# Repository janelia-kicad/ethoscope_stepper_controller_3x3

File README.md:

- [Repository Information](#org758a3eb)
  - [Description](#orgeb4be27)
- [Images](#org71172c4)
- [Schematic](#org945219d)
- [Gerbers](#org1d6248d)
- [Bill of Materials](#orgcc7b03c)
  - [PCB Parts](#orga3dccca)
  - [Supplemental Parts](#org7db11a9)
  - [Vendor Parts Lists](#orgad09c1d)
- [Supplemental Documentation](#org79a2346)
  - [Assembly Instructions](#org838f5a4)

# Repository Information

-   **Name:** ethoscope\_stepper\_controller\_3x3
-   **Version:** 1.2
-   **License:** Open-Source Hardware
-   **URL:** <https://github.com/janelia-kicad/ethoscope_stepper_controller_3x3>
-   **Author:** Peter Polidoro
-   **Email:** peter@polidoro.io

## Description

This device controls the 7 stepper motors on the fly ethoscope rig.

# Images

# Schematic

[./schematic/ethoscope\_stepper\_controller\_3x3.pdf](./schematic/ethoscope_stepper_controller_3x3.pdf)

# Gerbers

Send gerbers zip file to your favorite PCB manufacturer for fabrication.

[./gerbers/ethoscope\_stepper\_controller\_3x3\_v1.2.zip](./gerbers/ethoscope_stepper_controller_3x3_v1.2.zip)

# Bill of Materials

## PCB Parts

| Item | Reference(s)                                     | Quantity | PartNumber       | Vendor  | Description                      |
|---- |------------------------------------------------ |-------- |---------------- |------- |-------------------------------- |
| 1    | C1 C12 C13 C16 C19 C2 C22 C23 C3 C6 C9           | 11       | 1276-1739-1-ND   | digikey | CAP CER 0.1UF 25V Y5V 0402       |
| 2    | C10 C14 C17 C20 C24 C4 C7                        | 7        | 445-14419-1-ND   | digikey | CAP CER 10UF 35V X5R 0805        |
| 3    | C11 C15 C18 C21 C25 C5 C8                        | 7        | 445-9028-1-ND    | digikey | CAP CER 2.2UF 35V X5R 0402       |
| 4    | CLK1                                             | 1        | CTX277LVCT-ND    | digikey | OSC XO 32.000MHZ HCMOS TTL SMD   |
| 5    | L1                                               | 1        | 350-1723-ND      | digikey | LED 2MM 24V VERTICAL RED PC MNT  |
| 6    | L2                                               | 1        | 350-1726-ND      | digikey | LED 2MM 5V VERTICAL GREEN PC MNT |
| 7    | MH1 MH2 MH3 MH4                                  | 4        | 36-2441-ND       | digikey | SHLDR SCREW RND HEAD HEX 4-40    |
| 8    | P1                                               | 1        | CP-015AHPJ-CT-ND | digikey | CONN PWR JACK 2X5.5MM SOLDER     |
| 9    | R1 R15 R8                                        | 3        | P10KJCT-ND       | digikey | RES SMD 10K OHM 5% 1/10W 0402    |
| 10   | R10 R11 R12 R13 R14 R16 R17 R2 R3 R4 R5 R6 R7 R9 | 14       | RL05S2.2FCT-ND   | digikey | RES SMD 2.2 OHM 1% 1/6W 0402     |
| 11   | T1 T2 T3 T4 T5 T6 T7                             | 7        | 277-5738-ND      | digikey | TERM BLOCK HDR 4POS VERT 3.5MM   |
| 12   | TEENSY1                                          | 1        | 1568-1464-ND     | digikey | TEENSY 3.5 (HEADERS)             |
| 13   | U1 U11 U6                                        | 3        | 1460-1071-1-ND   | digikey | IC MOTOR CONTROLLER SPI 32QFN    |
| 14   | U10 U13 U3 U4 U5 U8 U9                           | 7        | 296-40083-1-ND   | digikey | IC MOTOR DRIVER PAR 24VQFN       |
| 15   | U12 U2 U7                                        | 3        | 296-11603-1-ND   | digikey | IC BUF NON-INVERT 5.5V SOT23-5   |

## Supplemental Parts

| Item | Quantity | PartNumber   | Vendor  | Description                      |
|---- |-------- |------------ |------- |-------------------------------- |
| 1    | 1        | 102-4531-ND  | digikey | AC-DC 18 VDC 2 A SW C14 DESK     |
| 2    | 1        | 1175-1298-ND | digikey | CORD PWR MALE-FEMALE STR 2M      |
| 3    | 1        | 1175-1694-ND | digikey | CABLE USB-A TO MICRO USB-B .5M   |
| 4    | 2        | 1212-1209-ND | digikey | SOCKET 7 MM SOLDER TAIL SINGLE   |
| 5    | 28       | 277-2433-ND  | digikey | FERRULES WITH PLASTIC SLEEVE YEL |
| 6    | 7        | 277-2418-ND  | digikey | TERM BLOCK PLUG 4POS STR 3.5MM   |
| 7    | 7        | P14333-ND    | digikey | STEP MOTOR PM GEARED BIPOLAR 15V |

## Vendor Parts Lists

[./bom/digikey\_parts.csv](./bom/digikey_parts.csv)

[./bom/supplemental\_digikey\_parts.csv](./bom/supplemental_digikey_parts.csv)

# Supplemental Documentation

## Assembly Instructions

-   Solder surface mount and through hole components onto the pcb.

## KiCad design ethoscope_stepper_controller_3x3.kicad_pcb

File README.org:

# Created 2019-02-06 Wed 09:52
#+OPTIONS: title:nil author:nil email:nil toc:t |:t ^:nil
* Repository Information

- Name :: ethoscope_stepper_controller_3x3
- Version :: 1.2
- License :: Open-Source Hardware
- URL :: https://github.com/janelia-kicad/ethoscope_stepper_controller_3x3
- Author :: Peter Polidoro
- Email :: peter@polidoro.io

** Description

This device controls the 7 stepper motors on the fly ethoscope rig.

* Images

* Schematic

[[file:./schematic/ethoscope_stepper_controller_3x3.pdf][./schematic/ethoscope_stepper_controller_3x3.pdf]]

[[file:./schematic/images/schematic00.png]]

[[file:./schematic/images/schematic01.png]]

[[file:./schematic/images/schematic02.png]]

[[file:./schematic/images/schematic03.png]]

[[file:./schematic/images/schematic04.png]]

[[file:./schematic/images/schematic05.png]]

[[file:./schematic/images/schematic06.png]]

[[file:./schematic/images/schematic07.png]]

[[file:./schematic/images/schematic08.png]]

[[file:./schematic/images/schematic09.png]]

[[file:./schematic/images/schematic10.png]]

[[file:./schematic/images/schematic11.png]]

* Gerbers

Send gerbers zip file to your favorite PCB manufacturer for fabrication.

[[file:./gerbers/ethoscope_stepper_controller_3x3_v1.2.zip][./gerbers/ethoscope_stepper_controller_3x3_v1.2.zip]]

[[file:./gerbers/images/gerbers00.png]]

[[file:./gerbers/images/gerbers01.png]]

* Bill of Materials

** PCB Parts

| Item | Reference(s)                                     | Quantity | PartNumber       | Vendor  | Description                      |
|------+--------------------------------------------------+----------+------------------+---------+----------------------------------|
|    1 | C1 C12 C13 C16 C19 C2 C22 C23 C3 C6 C9           |       11 | 1276-1739-1-ND   | digikey | CAP CER 0.1UF 25V Y5V 0402       |
|    2 | C10 C14 C17 C20 C24 C4 C7                        |        7 | 445-14419-1-ND   | digikey | CAP CER 10UF 35V X5R 0805        |
|    3 | C11 C15 C18 C21 C25 C5 C8                        |        7 | 445-9028-1-ND    | digikey | CAP CER 2.2UF 35V X5R 0402       |
|    4 | CLK1                                             |        1 | CTX277LVCT-ND    | digikey | OSC XO 32.000MHZ HCMOS TTL SMD   |
|    5 | L1                                               |        1 | 350-1723-ND      | digikey | LED 2MM 24V VERTICAL RED PC MNT  |
|    6 | L2                                               |        1 | 350-1726-ND      | digikey | LED 2MM 5V VERTICAL GREEN PC MNT |
|    7 | MH1 MH2 MH3 MH4                                  |        4 | 36-2441-ND       | digikey | SHLDR SCREW RND HEAD HEX 4-40    |
|    8 | P1                                               |        1 | CP-015AHPJ-CT-ND | digikey | CONN PWR JACK 2X5.5MM SOLDER     |
|    9 | R1 R15 R8                                        |        3 | P10KJCT-ND       | digikey | RES SMD 10K OHM 5% 1/10W 0402    |
|   10 | R10 R11 R12 R13 R14 R16 R17 R2 R3 R4 R5 R6 R7 R9 |       14 | RL05S2.2FCT-ND   | digikey | RES SMD 2.2 OHM 1% 1/6W 0402     |
|   11 | T1 T2 T3 T4 T5 T6 T7                             |        7 | 277-5738-ND      | digikey | TERM BLOCK HDR 4POS VERT 3.5MM   |
|   12 | TEENSY1                                          |        1 | 1568-1464-ND     | digikey | TEENSY 3.5 (HEADERS)             |
|   13 | U1 U11 U6                                        |        3 | 1460-1071-1-ND   | digikey | IC MOTOR CONTROLLER SPI 32QFN    |
|   14 | U10 U13 U3 U4 U5 U8 U9                           |        7 | 296-40083-1-ND   | digikey | IC MOTOR DRIVER PAR 24VQFN       |
|   15 | U12 U2 U7                                        |        3 | 296-11603-1-ND   | digikey | IC BUF NON-INVERT 5.5V SOT23-5   |

** Supplemental Parts

| Item | Quantity | PartNumber   | Vendor  | Description                      |
|------+----------+--------------+---------+----------------------------------|
|    1 |        1 | 102-4531-ND  | digikey | AC-DC 18 VDC 2 A SW C14 DESK     |
|    2 |        1 | 1175-1298-ND | digikey | CORD PWR MALE-FEMALE STR 2M      |
|    3 |        1 | 1175-1694-ND | digikey | CABLE USB-A TO MICRO USB-B .5M   |
|    4 |        2 | 1212-1209-ND | digikey | SOCKET 7 MM SOLDER TAIL SINGLE   |
|    5 |       28 | 277-2433-ND  | digikey | FERRULES WITH PLASTIC SLEEVE YEL |
|    6 |        7 | 277-2418-ND  | digikey | TERM BLOCK PLUG 4POS STR 3.5MM   |
|    7 |        7 | P14333-ND    | digikey | STEP MOTOR PM GEARED BIPOLAR 15V |

** Vendor Parts Lists

[[file:./bom/digikey_parts.csv][./bom/digikey_parts.csv]]

[[file:./bom/supplemental_digikey_parts.csv][./bom/supplemental_digikey_parts.csv]]

* Supplemental Documentation

** Assembly Instructions

- Solder surface mount and through hole components onto the pcb.

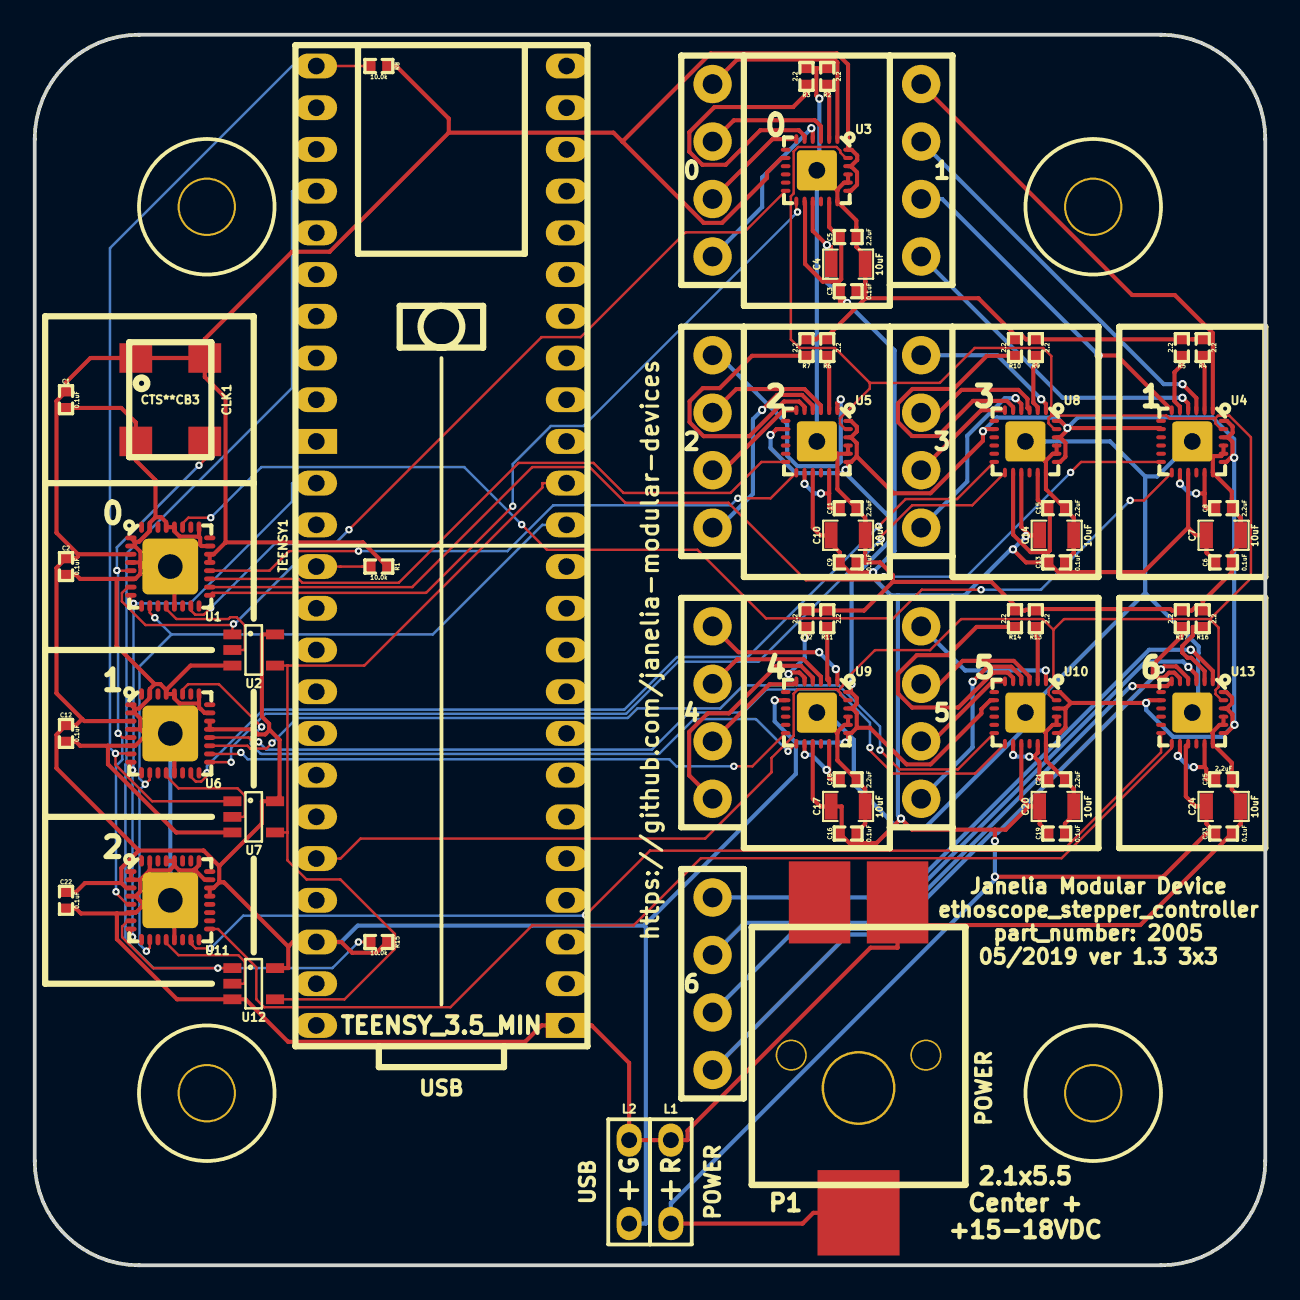
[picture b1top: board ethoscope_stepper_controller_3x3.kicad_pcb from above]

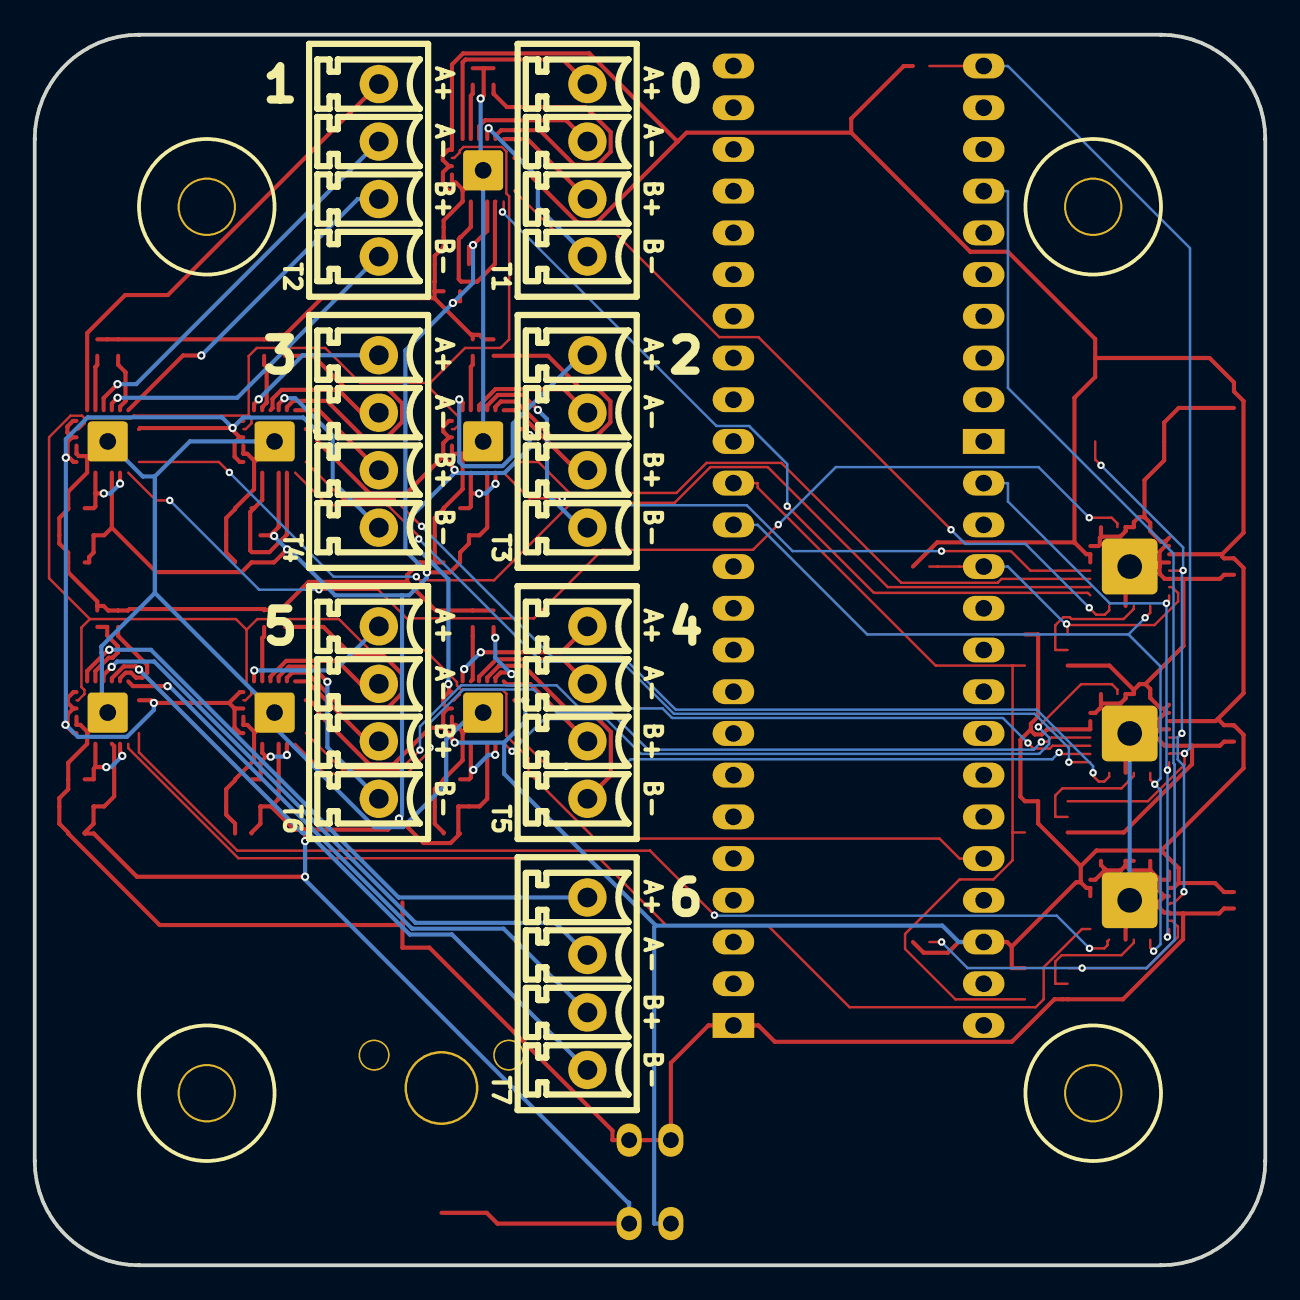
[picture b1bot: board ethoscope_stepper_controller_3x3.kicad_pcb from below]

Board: 2 copper layers, 74.9 x 74.9 mm, 71 parts (7 on the bottom side), 77 nets.

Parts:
C1, C2, C3, C6, C9, C12, C13, C16, C19, C22, C23: 0.1uF; SM0402
C4, C7, C10, C14, C17, C20, C24: 10uF; SM0805
C5, C8, C11, C15, C18, C21, C25: 2.2uF; SM0402
CLK1: CLK_32MHZ; CTS_SMD_4_7X5MM
L1: LED_24V_RED; LED_555-3XXX_R
L2: LED_5V_GRN; LED_555-3XXX_G
MH1, MH2, MH3, MH4: MOUNT_HOLE; MOUNTING_HOLE_4-40
P1: PWR_JACK_2.1x5.5_SMD_VERT; DCJACK_3PIN_SMD_VERT
R1, R8, R15: 10.0k; SM0402
R2, R3, R4, R5, R6, R7, R9, R10, R11, R12, R13, R14, R16, R17: 2.2; SM0402
T1, T2, T3, T4, T5, T6, T7: TERM_BLK_HDR_4POS_VERT_0.138IN
TEENSY1: TEENSY_3.5_MIN
U1, U6, U11: TMC429; QFN-5x5-32
U2, U7, U12: BUFFER_TRI_STATE; SOT-23-5
U3, U4, U5, U8, U9, U10, U13: DRV8846; VQFN-4x4-24

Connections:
+3V3: C1.1, C2.1, C12.1, C22.1, CLK1.1, CLK1.4, L2.1, R1.1, R8.1, R15.1, TEENSY1.3V3, U1.3, U1.21, U1.22, U2.5, U3.8, U3.19, U3.22, U3.24, U4.8, U4.19, U4.22, U4.24, U5.8, U5.19, U5.22, U5.24, U6.3, U6.21, U6.22, U7.5, U8.8, U8.19, U8.22, U8.24, U9.8, U9.19, U9.22, U9.24, U10.8, U10.19, U10.22, U10.24, U11.3, U11.21, U11.22, U12.5, U13.8, U13.19, U13.22, U13.24
/MISO: TEENSY1.12, U2.4, U7.4, U12.4
/MOSI: TEENSY1.11, U1.10, U6.10, U11.10
/SCK: TEENSY1.13, U1.8, U6.8, U11.8
/ethoscope_3x3/CLK: CLK1.3, U1.5, U6.5, U11.5
/ethoscope_3x3/tmc429_0/DIR_0: U1.17, U3.13
/ethoscope_3x3/tmc429_0/DIR_1: U1.27, U4.13
/ethoscope_3x3/tmc429_0/DIR_2: U1.20, U5.13
/ethoscope_3x3/tmc429_0/MISO_UB: U1.12, U2.2
/ethoscope_3x3/tmc429_0/STEP_0: U1.15, U3.12
/ethoscope_3x3/tmc429_0/STEP_1: U1.18, U4.12
/ethoscope_3x3/tmc429_0/STEP_2: U1.19, U5.12
/ethoscope_3x3/tmc429_0/stepper_driver_0/AISEN: R2.1, U3.2
/ethoscope_3x3/tmc429_0/stepper_driver_0/A_+: T1.4, U3.1
/ethoscope_3x3/tmc429_0/stepper_driver_0/A_-: T1.3, U3.3
/ethoscope_3x3/tmc429_0/stepper_driver_0/BISEN: R3.1, U3.5
/ethoscope_3x3/tmc429_0/stepper_driver_0/B_+: T1.2, U3.6
/ethoscope_3x3/tmc429_0/stepper_driver_0/B_-: T1.1, U3.4
/ethoscope_3x3/tmc429_0/stepper_driver_0/VINT: C5.1, U3.14, U3.17
/ethoscope_3x3/tmc429_0/stepper_driver_1/AISEN: R4.1, U4.2
/ethoscope_3x3/tmc429_0/stepper_driver_1/A_+: T2.4, U4.1
/ethoscope_3x3/tmc429_0/stepper_driver_1/A_-: T2.3, U4.3
/ethoscope_3x3/tmc429_0/stepper_driver_1/BISEN: R5.1, U4.5
/ethoscope_3x3/tmc429_0/stepper_driver_1/B_+: T2.2, U4.6
/ethoscope_3x3/tmc429_0/stepper_driver_1/B_-: T2.1, U4.4
/ethoscope_3x3/tmc429_0/stepper_driver_1/VINT: C8.1, U4.14, U4.17
/ethoscope_3x3/tmc429_0/stepper_driver_2/AISEN: R6.1, U5.2
/ethoscope_3x3/tmc429_0/stepper_driver_2/A_+: T3.4, U5.1
/ethoscope_3x3/tmc429_0/stepper_driver_2/A_-: T3.3, U5.3
/ethoscope_3x3/tmc429_0/stepper_driver_2/BISEN: R7.1, U5.5
/ethoscope_3x3/tmc429_0/stepper_driver_2/B_+: T3.2, U5.6
/ethoscope_3x3/tmc429_0/stepper_driver_2/B_-: T3.1, U5.4
/ethoscope_3x3/tmc429_0/stepper_driver_2/VINT: C11.1, U5.14, U5.17
/ethoscope_3x3/tmc429_1/DIR_0: U6.17, U8.13
/ethoscope_3x3/tmc429_1/DIR_1: U6.27, U9.13
/ethoscope_3x3/tmc429_1/DIR_2: U6.20, U10.13
/ethoscope_3x3/tmc429_1/MISO_UB: U6.12, U7.2
/ethoscope_3x3/tmc429_1/STEP_0: U6.15, U8.12
/ethoscope_3x3/tmc429_1/STEP_1: U6.18, U9.12
/ethoscope_3x3/tmc429_1/STEP_2: U6.19, U10.12
/ethoscope_3x3/tmc429_1/stepper_driver_0/AISEN: R9.1, U8.2
/ethoscope_3x3/tmc429_1/stepper_driver_0/A_+: T4.4, U8.1
/ethoscope_3x3/tmc429_1/stepper_driver_0/A_-: T4.3, U8.3
/ethoscope_3x3/tmc429_1/stepper_driver_0/BISEN: R10.1, U8.5
/ethoscope_3x3/tmc429_1/stepper_driver_0/B_+: T4.2, U8.6
/ethoscope_3x3/tmc429_1/stepper_driver_0/B_-: T4.1, U8.4
/ethoscope_3x3/tmc429_1/stepper_driver_0/VINT: C15.1, U8.14, U8.17
/ethoscope_3x3/tmc429_1/stepper_driver_1/AISEN: R11.1, U9.2
/ethoscope_3x3/tmc429_1/stepper_driver_1/A_+: T5.4, U9.1
/ethoscope_3x3/tmc429_1/stepper_driver_1/A_-: T5.3, U9.3
/ethoscope_3x3/tmc429_1/stepper_driver_1/BISEN: R12.1, U9.5
/ethoscope_3x3/tmc429_1/stepper_driver_1/B_+: T5.2, U9.6
/ethoscope_3x3/tmc429_1/stepper_driver_1/B_-: T5.1, U9.4
/ethoscope_3x3/tmc429_1/stepper_driver_1/VINT: C18.1, U9.14, U9.17
/ethoscope_3x3/tmc429_1/stepper_driver_2/AISEN: R13.1, U10.2
/ethoscope_3x3/tmc429_1/stepper_driver_2/A_+: T6.4, U10.1
/ethoscope_3x3/tmc429_1/stepper_driver_2/A_-: T6.3, U10.3
/ethoscope_3x3/tmc429_1/stepper_driver_2/BISEN: R14.1, U10.5
/ethoscope_3x3/tmc429_1/stepper_driver_2/B_+: T6.2, U10.6
/ethoscope_3x3/tmc429_1/stepper_driver_2/B_-: T6.1, U10.4
/ethoscope_3x3/tmc429_1/stepper_driver_2/VINT: C21.1, U10.14, U10.17
/ethoscope_3x3/tmc_429_2/DIR_0: U11.17, U13.13
/ethoscope_3x3/tmc_429_2/MISO_UB: U11.12, U12.2
/ethoscope_3x3/tmc_429_2/STEP_0: U11.15, U13.12
/ethoscope_3x3/tmc_429_2/stepper_driver_0/AISEN: R16.1, U13.2
/ethoscope_3x3/tmc_429_2/stepper_driver_0/A_+: T7.4, U13.1
/ethoscope_3x3/tmc_429_2/stepper_driver_0/A_-: T7.3, U13.3
/ethoscope_3x3/tmc_429_2/stepper_driver_0/BISEN: R17.1, U13.5
/ethoscope_3x3/tmc_429_2/stepper_driver_0/B_+: T7.2, U13.6
/ethoscope_3x3/tmc_429_2/stepper_driver_0/B_-: T7.1, U13.4
/ethoscope_3x3/tmc_429_2/stepper_driver_0/VINT: C25.1, U13.14, U13.17
/~CS_429_0: R1.2, TEENSY1.15, U1.7, U2.1
/~CS_429_1: R8.2, TEENSY1.33, U6.7, U7.1
/~CS_429_2: R15.2, TEENSY1.36, U11.7, U12.1
/~SLEEP: TEENSY1.22, U3.23, U4.23, U5.23, U8.23, U9.23, U10.23, U13.23
GND: C1.2, C2.2, C3.2, C4.2, C5.2, C6.2, C7.2, C8.2, C9.2, C10.2, C11.2, C12.2, C13.2, C14.2, C15.2, C16.2, C17.2, C18.2, C19.2, C20.2, C21.2, C22.2, C23.2, C24.2, C25.2, CLK1.2, L1.2, L2.2, P1.2, R2.2, R3.2, R4.2, R5.2, R6.2, R7.2, R9.2, R10.2, R11.2, R12.2, R13.2, R14.2, R16.2, R17.2, TEENSY1.GND, U1.1, U1.2, U1.4, U1.6, U1.13, U1.23, U1.25, U1.28, U1.29, U1.31, U1.PAD, U2.3, U3.18, U3.20, U3.21, U3.PAD, U4.18, U4.20, U4.21, U4.PAD, U5.18, U5.20, U5.21, U5.PAD, U6.1, U6.2, U6.4, U6.6, U6.13, U6.23, U6.25, U6.28, U6.29, U6.31, U6.PAD, U7.3, U8.18, U8.20, U8.21, U8.PAD, U9.18, U9.20, U9.21, U9.PAD, U10.18, U10.20, U10.21, U10.PAD, U11.1, U11.2, U11.4, U11.6, U11.13, U11.23, U11.25, U11.28, U11.29, U11.31, U11.PAD, U12.3, U13.18, U13.20, U13.21, U13.PAD
VAA: C3.1, C4.1, C6.1, C7.1, C9.1, C10.1, C13.1, C14.1, C16.1, C17.1, C19.1, C20.1, C23.1, C24.1, L1.1, P1.1, U3.15, U4.15, U5.15, U8.15, U9.15, U10.15, U13.15

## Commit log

2018-08-12 Initial commit.
2018-08-12 Added files from step_dir_controller.
2018-08-13 Added teensy to schematic.
2018-08-13 Added power jack.
2018-08-14 Added sense resistors.
2018-08-14 Renamed schematics.
2018-08-14 Finished schematics.
2018-08-14 Annotated schematics.
2018-08-14 Fixed footprints.
2018-08-14 Initial layout.
2018-08-15 Switched to 0805 parts.
2018-08-15 Added a pull-up resistor and tri-state buffer.
2018-08-15 Placed more parts, but saved with errors.
2018-08-21 Initial part placement.
2018-08-21 Use 0402 parts when possible.
2018-08-22 Added autorouted tracks.
2018-08-22 Moved traces to pass bug check.
2018-08-22 ethoscope_stepper_controller -> ethoscope_stepper_controller_3x3.
2018-08-22 Finished version 1.0.
2018-08-22 Generated documentation.
2018-08-22 Updated submodules.
2018-08-23 Added digikey_order.
2018-08-24 Removed F.SilkS from pads.
2018-09-11 Fixed error in supplemental bom.
2018-09-14 Added motors to bom.
2018-09-18 Rearranged schematics.
2018-09-18 Ready for autorouting.
2018-09-19 Finished autorouting.
2018-09-19 Updated documentation.
2018-09-19 v1.0 -> v1.1.
2018-09-19 Fixed version error.
2018-11-02 Added README.md.
2019-01-04 Switch current sense resistor from 5.1 to 3.3
2019-02-05 Progress towards v1.2
2019-02-06 Update documentation
2019-04-22 Progress towards v1.3
2019-05-06 Update date
2021-09-16 Update email address
2021-09-21 Remove ignored files
2022-02-22 Add guix files
2022-02-23 Add guix documentation
